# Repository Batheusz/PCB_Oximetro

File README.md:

# PCB_Oximetro
 Projeto da disciplina de Desenho Tecnico Aplicado da UTFPR-CT

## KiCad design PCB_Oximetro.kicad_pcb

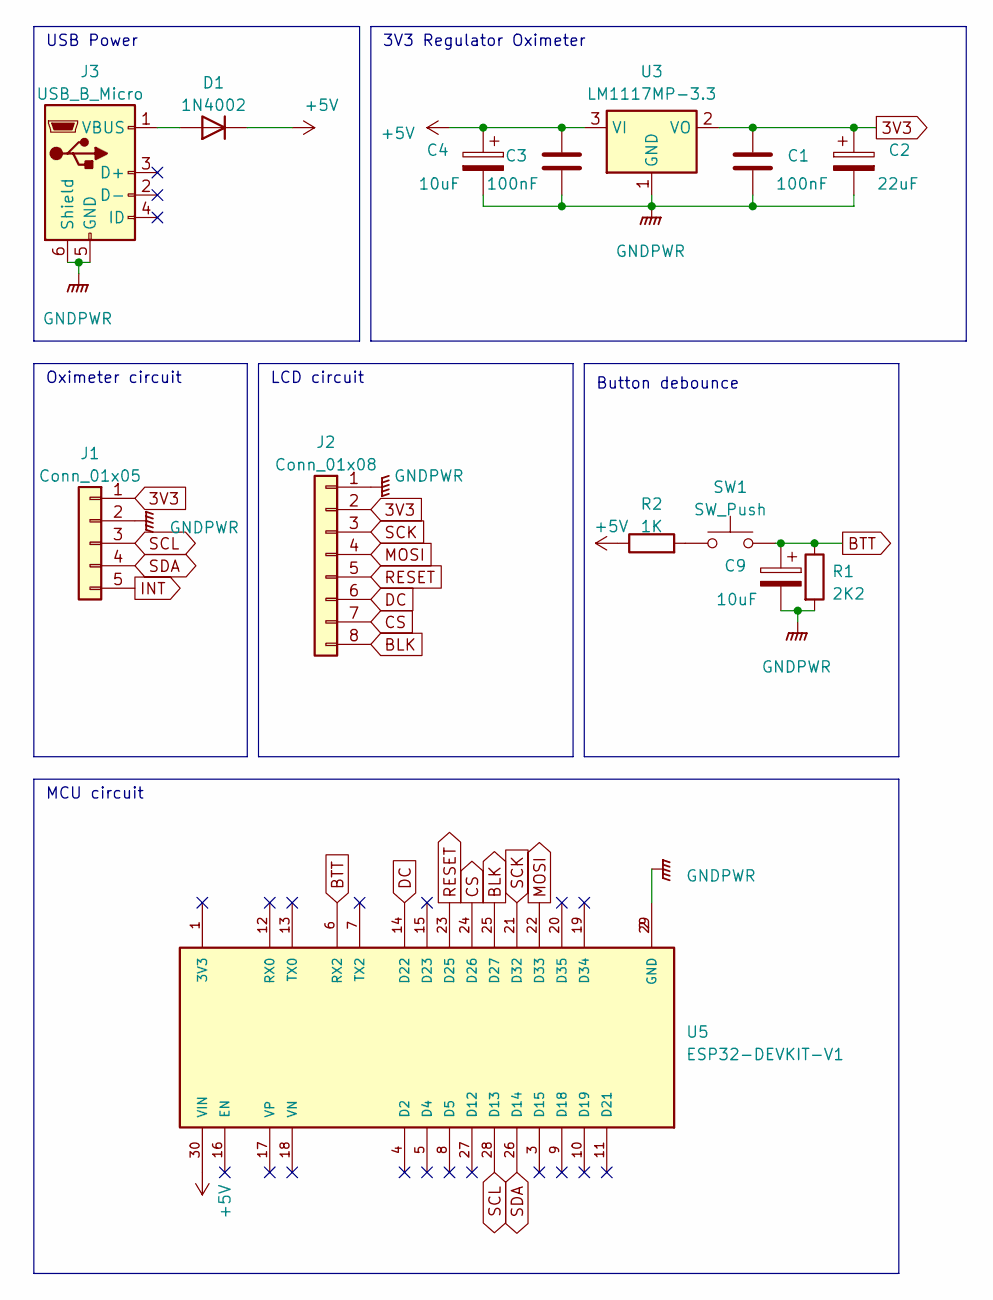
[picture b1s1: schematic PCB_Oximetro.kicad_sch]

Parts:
C1, C3: 100nF; C_0805_2012Metric
C2: 22uF; CP_Radial_Tantal_D5.0mm_P2.50mm
C4, C9: 10uF; CP_Radial_D5.0mm_P2.50mm
D1: 1N4002; D_DO-41_SOD81_P10.16mm_Horizontal
J1: Conn_01x05; PinSocket_1x05_P2.54mm_Vertical
J2: Conn_01x08; PinSocket_1x08_P2.54mm_Vertical
J3: USB_B_Micro; USB_Micro-B_Amphenol_10104110_Horizontal
R1: 2K2; R_1206_3216Metric
R2: 1K; R_1206_3216Metric
SW1: SW_Push; SW_Tactile_SPST_Angled_PTS645Vx58-2LFS
U3: LM1117MP-3.3; SOT-223-3_TabPin2
U5: ESP32-DEVKIT-V1; MODULE_ESP32_DEVKIT_V1; PARTREV N/A

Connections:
3V3: C1.1, C2.1, J1.1, J2.2, U3.2 (VO)
+5V: C3.1, C4.1, D1.1 (K), R2.1, U3.3 (VI), U5.30 (VIN)
BLK: J2.8, U5.25 (D27)
BTT: C9.1, R1.1, SW1.2, U5.6 (RX2)
CS: J2.7, U5.24 (D26)
DC: J2.6, U5.14 (D22)
GNDPWR: C1.2, C2.2, C3.2, C4.2, C9.2, J1.2, J2.1, J3.5 (GND), J3.6 (Shield), R1.2, U3.1 (GND), U5.2 (GND), U5.29 (GND)
INT: J1.5
MOSI: J2.4, U5.22 (D33)
unnamed: D1.2 (A), J3.1 (VBUS)
unnamed: R2.2, SW1.1
RESET: J2.5, U5.23 (D25)
SCK: J2.3, U5.21 (D32)
SCL: J1.3, U5.28 (D13)
SDA: J1.4, U5.26 (D14)

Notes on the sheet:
MCU circuit
Button debounce
USB Power
Oximeter circuit
LCD circuit
3V3 Regulator Oximeter

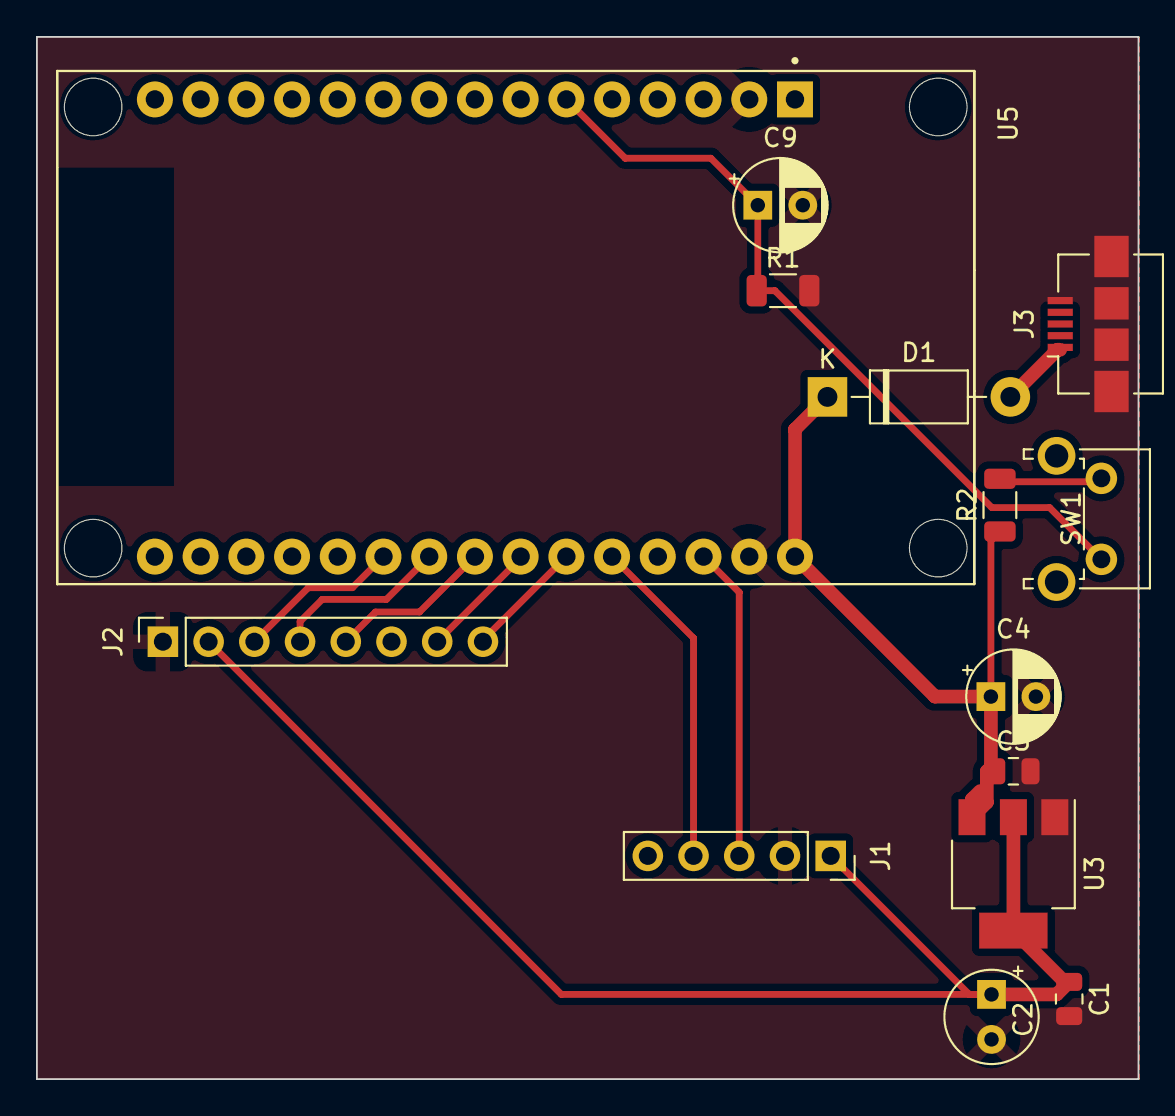
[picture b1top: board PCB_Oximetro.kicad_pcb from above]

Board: 2 copper layers, 61.2 x 57.9 mm, 14 parts (0 on the bottom side), 14 nets.

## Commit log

2023-09-04 Voltage regulators
    Added voltage regulators for ESP-32 and MAX30102
2023-09-04 MCU, LCD and MAX30102
    Added ESP32, LCD and MAX30102 schematics
2023-09-05 1st PCB
    1st PCB layout
    Regulators change
    LCD pins adjust
2023-09-05 PCB Layout
    2nd PCB Layout (Without revision with professor)
2023-09-05 3rd PCB Layout
2023-09-05 4th PCB Layout
2023-09-05 3D Case
    Adaptions for 3D Case
2023-09-05 I2C Adjust
    Added I2C and INT pull up resistor
2023-09-07 USB change
    Change USB for mini USB and removed fuse
2023-09-07 Oximeter change
    Removed MAX30102 sensor and added MAX30102 shield
2023-09-07 PCB Layout
    Changed pcb layout for MAX30102 module
2023-09-07 Modelagem 3D
2023-09-08 GPIO12 change
    GPIO12 change because of ESP32 boot
2023-09-08 BTT pin
    Changed BTT pin because of boot
2023-09-12 1.0.0v
    Plot Gerbers files
2023-09-17 BTT Update
2023-10-03 Update MISO
    MISO Removed for compatibility
2023-10-03 Capacitor size change
    Changed capacitor smd 1206 to 0805 because of availibility
2023-10-03 BLK Pin update
    Changed BLK pin to make the PCB 1 only front layer
2023-10-03 Gerbers file
    Generated gerbers files and drill
2023-10-10 Update PCB
